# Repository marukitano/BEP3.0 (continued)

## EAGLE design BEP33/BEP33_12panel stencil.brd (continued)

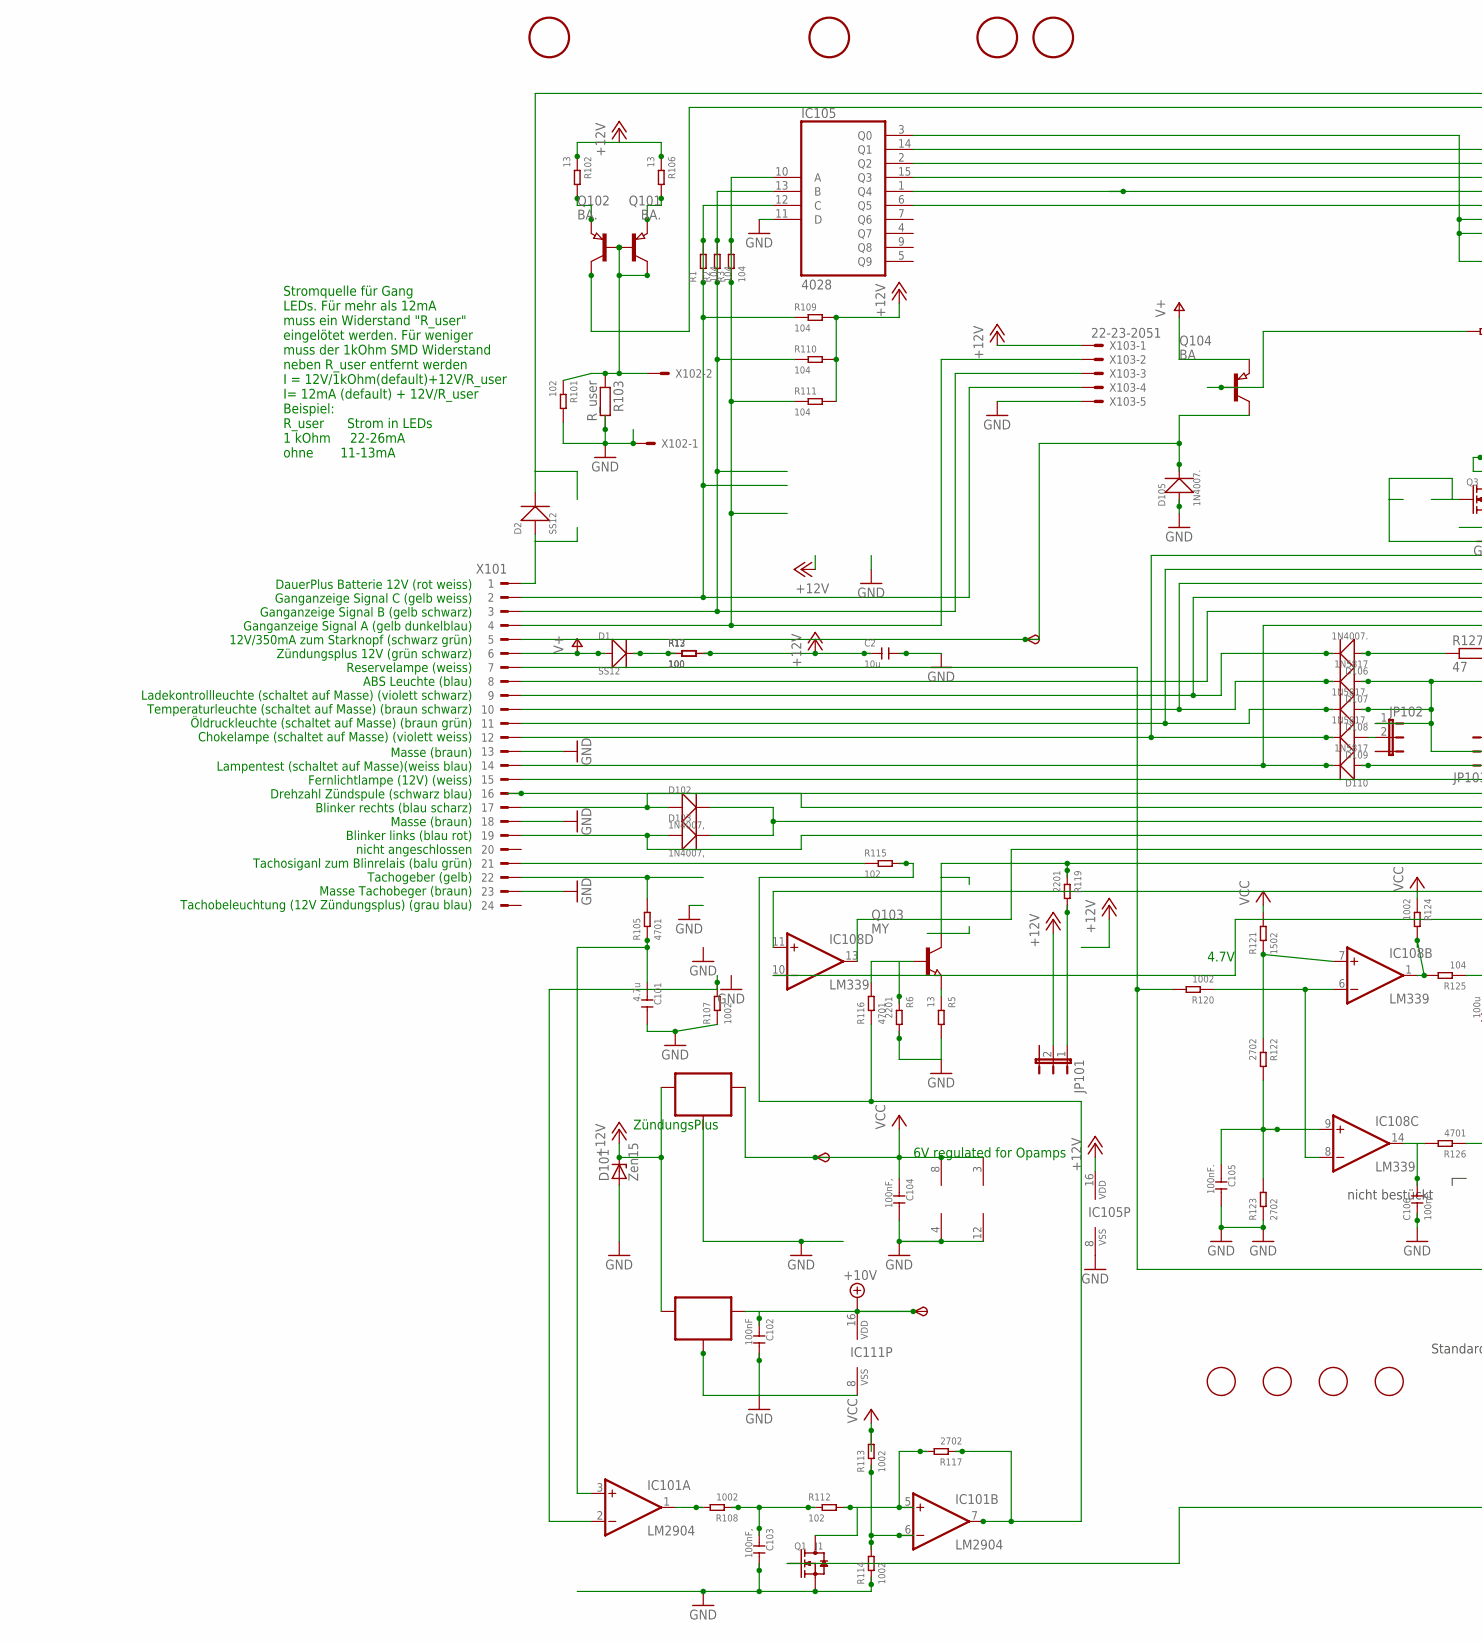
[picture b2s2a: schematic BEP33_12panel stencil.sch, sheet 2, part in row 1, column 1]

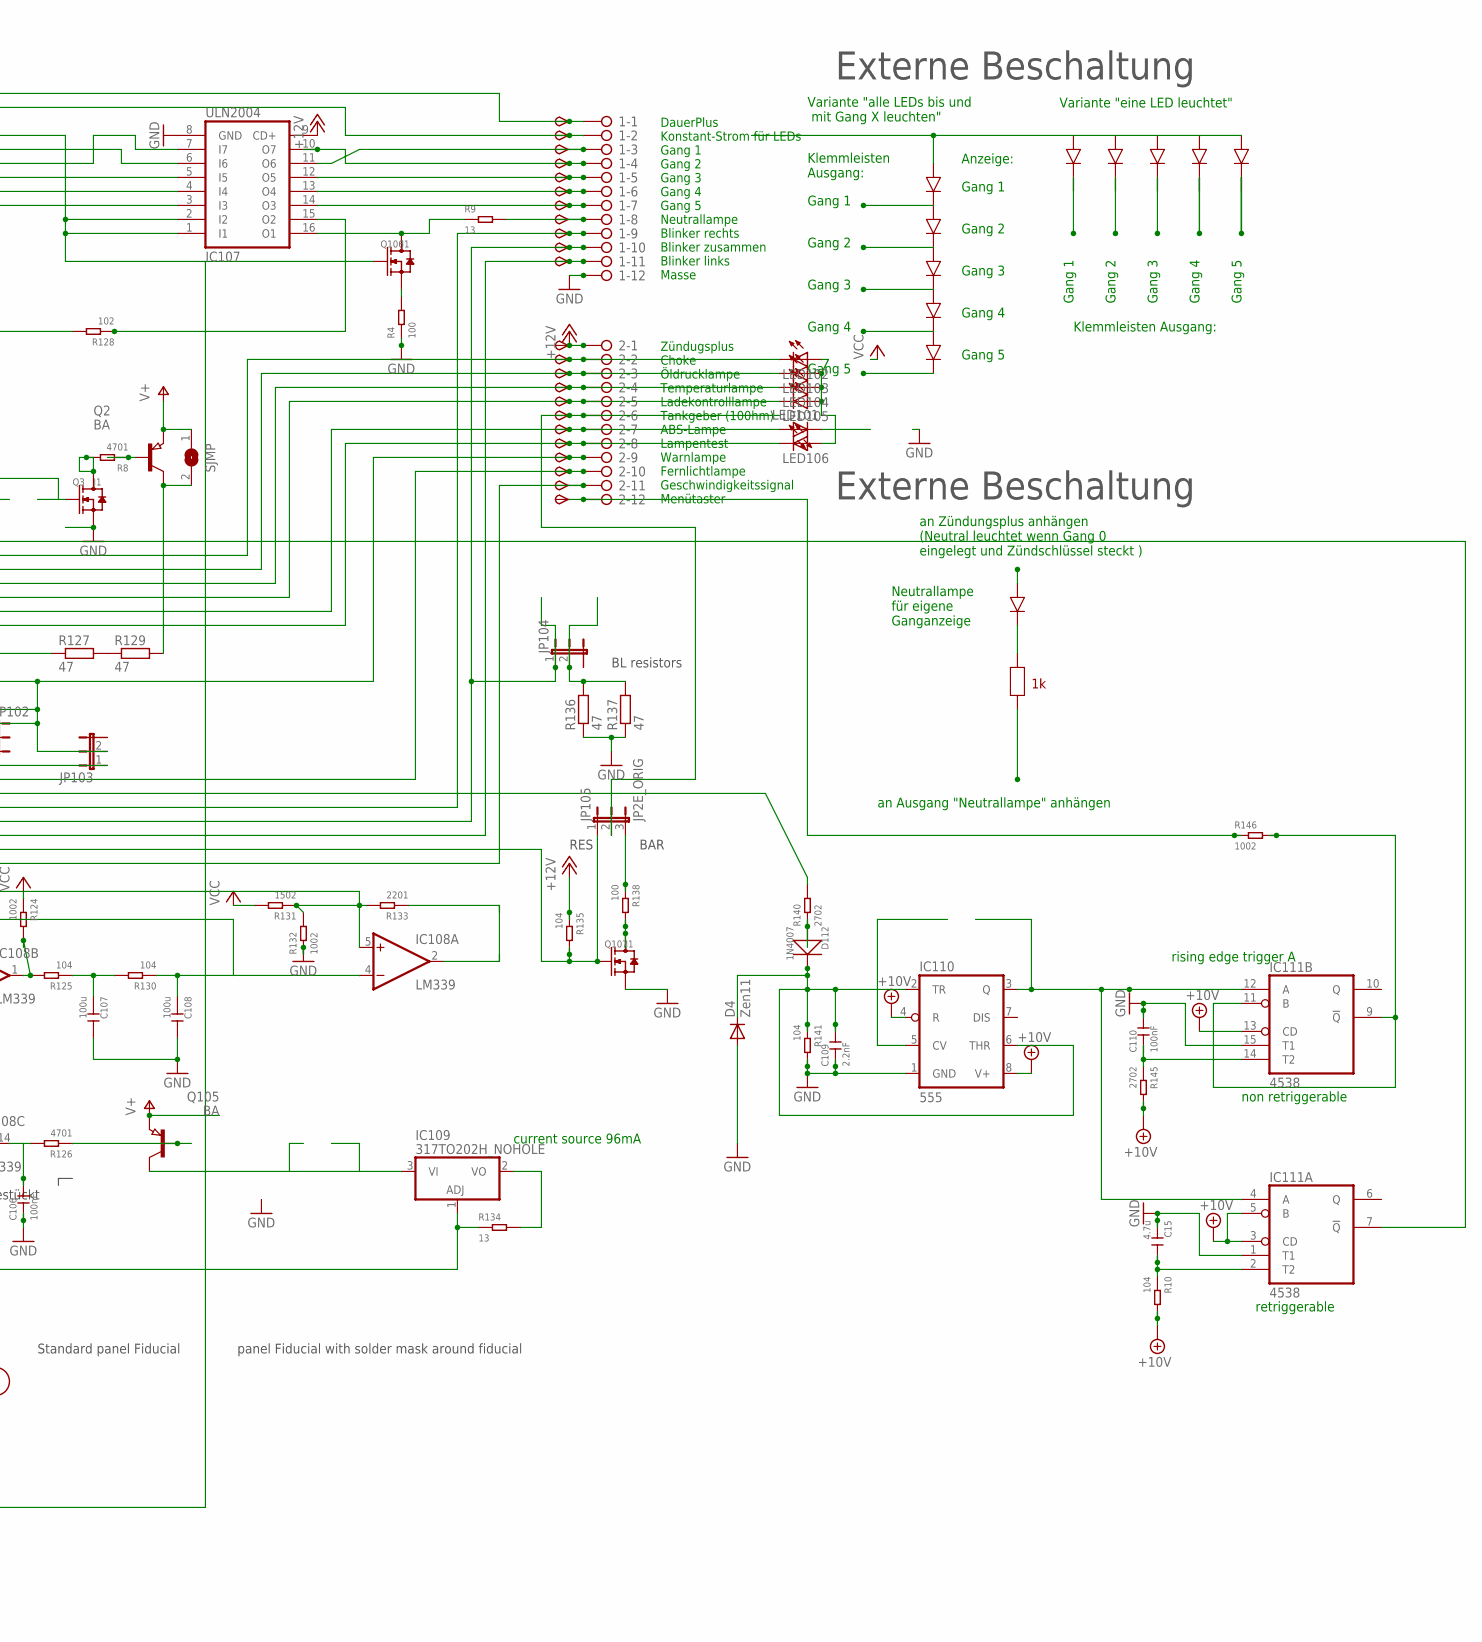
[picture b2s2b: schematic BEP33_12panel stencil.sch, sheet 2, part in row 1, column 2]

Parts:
1, 2: 2081-1132; 12-PIN
6V, 10V: TPSB2.0; B2.0
C2: 10u; C1206
C15, C101: 4.7u; C0805
C102, C110: 100nF; C0805
C103, C104: 100nF,; C0805
C105, C106: 100nF.; C0805
C107, C108: 100u; C1206
C109: 2.2nF; C0805
D1, D2: SS12; DO-214AC_SLIM
D4: Zen11; SOD-123_MINI-SMA
D101: Zen15; DO214AA
D102, D103: 1N4007,; DO-214AC
D105, D106: 1N4007.; DO-214AC
D107, D110: 1N5817; DO-214AC_SLIM
D108, D109: 1N5817.; DO-214AC_SLIM
D112: 1N4007; DO-214AC
FID101, FID102, FID103, FID104: FIDUCIAL; FIDUCIAL_1MM
IC101: LM2904; SO08
IC102: 78L06; SOT89_ROUND
IC104: 78L10; SOT89_ROUND
IC105: 4028; SO16
IC107: ULN2004; SO16
IC108: LM339; SO14
IC109: 317TO202H_NOHOLE; TO220H_NOHOLE
IC110: 555; SO08
IC111: 4538; SO16
JP101, JP102, JP103, JP104: JP2EJP2_SMALLPADS; JP2_SMALLPADS
JP105: JP2E_ORIG; JP2_ORIG_SMALLPADS
LED101, LED102, LED103, LED104, LED105, LED106: LEDLD260; LD260
Q1, Q3, Q106, Q107: J1; SOT-23
Q2, Q104, Q105: BA; SOT89
Q101, Q102: BA.; SOT89
Q103: MY; SOT89
R1, R2, R3, R10, R109, R110, R111, R125, R130, R135, R141: 104; R0805
R4, R12, R13, R138: 100; R0805
R5, R9, R102, R106, R134: 13; R1206
R6, R119, R133: 2201; R0805
R8, R105, R116, R126: 4701; R0805
R101, R112, R115, R128: 102; R0805
R103: R_user; R0805
R107, R108, R113, R114, R120, R124, R132, R146: 1002; R0805
R117, R122, R123, R140, R145: 2702; R0805
R121, R131: 1502; R0805
R127, R129, R136, R137: 47; V235/17_1MM
SJMP: SJ
START: TPSB2.0; B2.0
TP1, TP2, TP3, TP4, TP5, TP6, TP7, TP8, TP9, TP10, TP11, TP12, TP13, TP16, TP17, TP18, TP19, TP21, TP22, TP23, TP25, TP26: TPSB2.0; B2.0
TP24: TPSB1,27; B1,27
U$13, U$18, U$21, U$22: STC; STENCIL_HOLE
X101: CON_BMWV2; 24-PIN_V2
X102: 22-23-2021
X103: 22-23-2051

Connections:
+10V: 10V.TP, C102.1, IC104.1 (OUT), IC110.4 (R), IC110.8 (V+), IC111.3 (CD), IC111.5 (B), IC111.13 (CD), IC111.16 (VDD), R10.2, R145.2; also elsewhere on the board
+12V: 2.1, C2.1, D101.C, IC102.3 (IN), IC104.3 (IN), IC105.16 (VDD), IC107.9 (CD+), JP101.2, R12.2, R13.2, R102.1, R106.1, R109.2, R110.2, R111.2, R135.1, TP12.TP, X103.1; also elsewhere on the board
+12V1: 2.11, Q103.2 (C), R119.1, TP26.TP
GND: 1.12, C2.2, C15.1, C101.2, C102.2, C103.2, C104.2, C105.2, C106.1, C107.2, C108.2, C109.1, C110.2, D4.A, D101.A, D105.1 (+), IC101.4 (V-), IC102.2 (GND), IC102.2@1 (GND), IC104.2 (GND), IC104.2@1 (GND), IC105.8 (VSS), IC105.11 (D), IC107.8 (GND), IC108.12 (GND), IC110.1 (GND), IC111.1 (T1), IC111.8 (VSS), IC111.15 (T1), Q1.2 (S), Q3.2 (S), Q107.2 (S), R4.1, R5.2, R6.2, R101.2, R103.2, R107.1, R114.1, R123.1, R132.1, R136.1, R137.1, R141.2, X101.13, X101.18, X101.23, X102.1, X103.5; also elsewhere on the board
unnamed: 2.9, D107.1 (+), D108.1 (+), JP102.1, JP103.2, TP24.TP
unnamed: IC105.10 (A), R3.1, R3.2, R111.1, X101.4, X103.2
unnamed: IC105.13 (B), R2.1, R2.2, R110.1, X101.3, X103.3
unnamed: 2.7, LED101.A, TP22.TP, X101.8
unnamed: Q101.3 (E), R102.2
unnamed: Q2.1 (B), R8.1
unnamed: IC101.2 (-IN), R107.2
unnamed: R127.2, R129.1
unnamed: Q102.3 (E), R106.2
unnamed: D105.2 (-), Q104.2 (C), START.TP, X101.5
unnamed: 2.2, D109.2 (-), LED102.K (C), TP16.TP, X101.12
unnamed: 2.3, D108.2 (-), LED103.K (C), TP17.TP, X101.11
unnamed: 2.4, D107.2 (-), LED104.K (C), TP18.TP, X101.10
unnamed: IC109.3 (VI), Q105.2 (C)
unnamed: IC108.6 (-IN), IC108.8 (-IN), R120.1
unnamed: IC105.12 (C), R1.1, R1.2, R109.1, X101.2, X103.4
unnamed: IC105.15 (Q3), IC107.5 (I5)
unnamed: 2.8, D110.2 (-), LED106.K (C), TP23.TP, X101.14
unnamed: 1.9, D102.1 (+), TP9.TP, X101.17
unnamed: 1.11, D103.1 (+), TP11.TP, X101.19
unnamed: IC111.9 (!Q), IC111.11 (B), R146.2
unnamed: R105.2, X101.22
unnamed: C101.1, IC101.3 (+IN), R105.1
unnamed: 1.6, IC107.13 (O4), TP6.TP
unnamed: 1.7, IC107.14 (O3), TP7.TP
unnamed: D1.2 (-), R12.1, R13.1
unnamed: 2.6, JP105.2, TP21.TP
unnamed: JP101.1, R119.2
unnamed: C105.1, IC108.9 (+IN), R122.2, R123.2
unnamed: C106.2, IC108.14 (OUT), R126.2
unnamed: Q3.3 (D), R8.2
unnamed: IC109.1 (ADJ), R120.2, R134.1, X101.7
unnamed: Q105.1 (B), R126.1
unnamed: IC105.2 (Q2), IC107.7 (I7)
unnamed: 1.3, IC107.11 (O6), TP3.TP
unnamed: 1.5, IC107.12 (O5), TP5.TP
unnamed: LED102.A, LED103.A, LED104.A, LED105.A, LED106.A
unnamed: R140.2, X101.16
unnamed: Q104.1 (B), R128.2
unnamed: IC105.3 (Q0), IC107.1 (I1), IC107.2 (I2), Q1.1 (G), Q106.1 (G)
unnamed: C107.1, R125.1, R130.2
unnamed: C108.1, IC108.4 (-IN), IC108.10 (-IN), R130.1
unnamed: IC108.5 (+IN), IC108.11 (+IN), R131.1, R132.2, R133.2
unnamed: Q107.3 (D), R138.2
unnamed: IC111.7 (!Q), Q3.1 (G)
unnamed: IC105.1 (Q4), IC107.4 (I4)
unnamed: R115.1, X101.21
unnamed: IC107.16 (O1), Q106.3 (D), R9.1
unnamed: 2.10, TP25.TP, X101.15
unnamed: D106.1 (+), R127.1
unnamed: 2.5, D106.2 (-), LED105.K (C), TP19.TP, X101.9
unnamed: IC105.14 (Q1), IC107.6 (I6)
unnamed: Q101.1 (B), Q102.1 (B), Q102.2 (C), R101.1, R103.1, X102.2
unnamed: 1.8, R9.2, TP8.TP
unnamed: 1.2, Q101.2 (C), TP2.TP
unnamed: IC108.13 (OUT), JP105.1, Q107.1 (G), R135.2
unnamed: IC105.6 (Q5), IC107.3 (I3)
unnamed: IC109.2 (VO), R134.2
unnamed: 1.4, IC107.10 (O7), TP4.TP
unnamed: 1.1, D2.2 (-), TP1.TP
unnamed: IC108.7 (+IN), R121.1, R122.1
unnamed: Q106.2 (S), R4.2
unnamed: Q103.1 (B), R6.1, R116.2
unnamed: IC110.3 (Q), IC111.4 (A), IC111.12 (A)
unnamed: D112.1 (+), R140.1
unnamed: IC107.15 (O2), R128.1
unnamed: C110.1, IC111.14 (T2), R145.1
unnamed: 2.12, R146.1, TP13.TP
unnamed: D2.1 (+), X101.1
unnamed: IC101.1 (OUT), R108.2
unnamed: 1.10, D102.2 (-), D103.2 (-), JP104.1, TP10.TP
unnamed: JP104.2, R136.2, R137.2
unnamed: D109.1 (+), JP102.2
unnamed: C103.1, R108.1, R112.1
unnamed: IC101.5 (+IN), Q1.3 (D), R112.2, R117.2
unnamed: D110.1 (+), JP103.1
unnamed: JP105.3, R138.1
unnamed: Q103.3 (E), R5.1
unnamed: IC101.6 (-IN), R113.1, R114.2
unnamed: C109.2, D4.C, D112.2 (-), IC110.2 (TR), IC110.6 (THR), R141.1
unnamed: C15.2, IC111.2 (T2), R10.1
unnamed: Q2.2 (C), R129.2, SJMP.2
unnamed: IC101.7 (OUT), R115.2, R116.1, R117.1
unnamed: IC108.2 (OUT), R133.1
unnamed: IC108.1 (OUT), R124.2, R125.2
V+: D1.1 (+), Q2.3 (E), Q104.3 (E), Q105.3 (E), SJMP.1, X101.6; also elsewhere on the board
VCC: 6V.TP, C104.1, IC101.8 (V+), IC102.1 (OUT), IC108.3 (V+), R113.2, R121.2, R124.1, R131.2; also elsewhere on the board

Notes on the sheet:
6V regulated for Opamps
current source 96mA
ZündungsPlus
Zündugsplus Choke Öldrucklampe Temperaturlampe Ladekontrolllampe Tankgeber (100hm) ABS-Lampe Lampentest Warnlampe Fernlichtlampe Geschwindigkeitssignal Menütaster
DauerPlus Konstant-Strom für LEDs Gang 1 Gang 2 Gang 3 Gang 4 Gang 5 Neutrallampe Blinker rechts Blinker zusammen Blinker links Masse
DauerPlus Batterie 12V (rot weiss) Ganganzeige Signal C (gelb weiss) Ganganzeige Signal B (gelb schwarz) Ganganzeige Signal A (gelb dunkelblau) 12V/350mA zum Starknopf (schwarz grün) Zündungsplus 12V (grün schwarz) Reservelampe (weiss) ABS Leuchte (blau) Ladekontrollleuchte (schaltet auf Masse) (vi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
Masse (braun) Lampentest (schaltet auf Masse)(weiss blau) Fernlichtlampe (12V) (weiss) Drehzahl Zündspule (schwarz blau) Blinker rechts (blau scharz) Masse (braun) Blinker links (blau rot) nicht angeschlossen Tachosiganl zum Blinrelais (balu grün) Tachogeber (gelb) Masse Tachobeger (braun) Tachobel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
4.7V
Stromquelle für Gang LEDs. Für mehr als 12mA muss ein Widerstand "R_user" eingelötet werden. Für weniger muss der 1kOhm SMD Widerstand neben R_user entfernt werden I = 12V/1kOhm(default)+12V/R_user I= 12mA (default) + 12V/R_user Beispiel: R_user Strom in LEDs 1 kOhm 22-26mA ohne 11-13mA
Gang 1
Gang 2
Gang 3
Gang 4
Gang 5
Variante "eine LED leuchtet"
Variante "alle LEDs bis und mit Gang X leuchten"
Klemmleisten Ausgang:
Klemmleisten Ausgang:
an Zündungsplus anhängen (Neutral leuchtet wenn Gang 0 eingelegt und Zündschlüssel steckt )
an Ausgang "Neutrallampe" anhängen
Neutrallampe für eigene Ganganzeige
Externe Beschaltung
Anzeige:
nicht bestückt
rising edge trigger A
BAR
RES
BL resistors
Standard panel Fiducial
panel Fiducial with solder mask around fiducial
non retriggerable
retriggerable

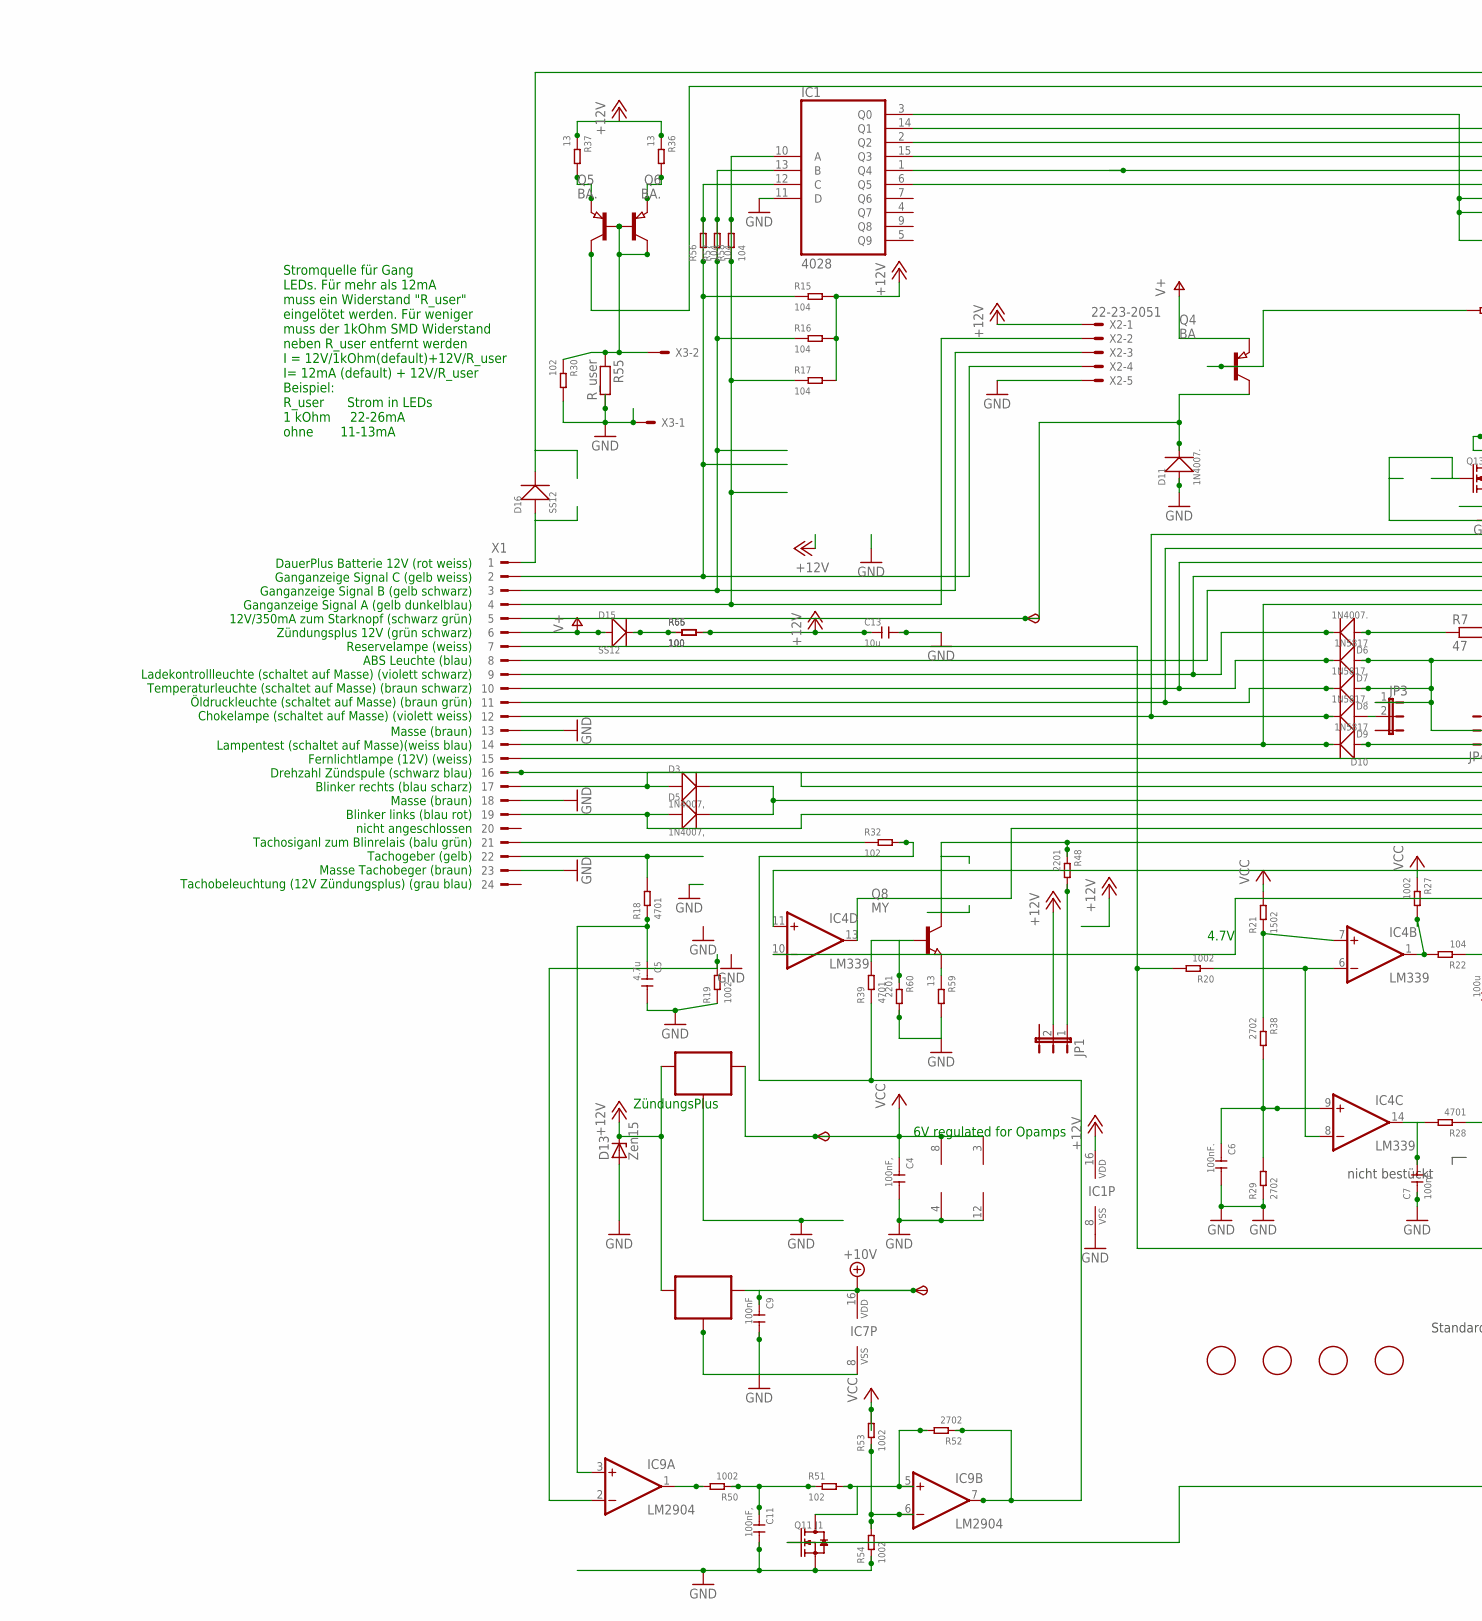
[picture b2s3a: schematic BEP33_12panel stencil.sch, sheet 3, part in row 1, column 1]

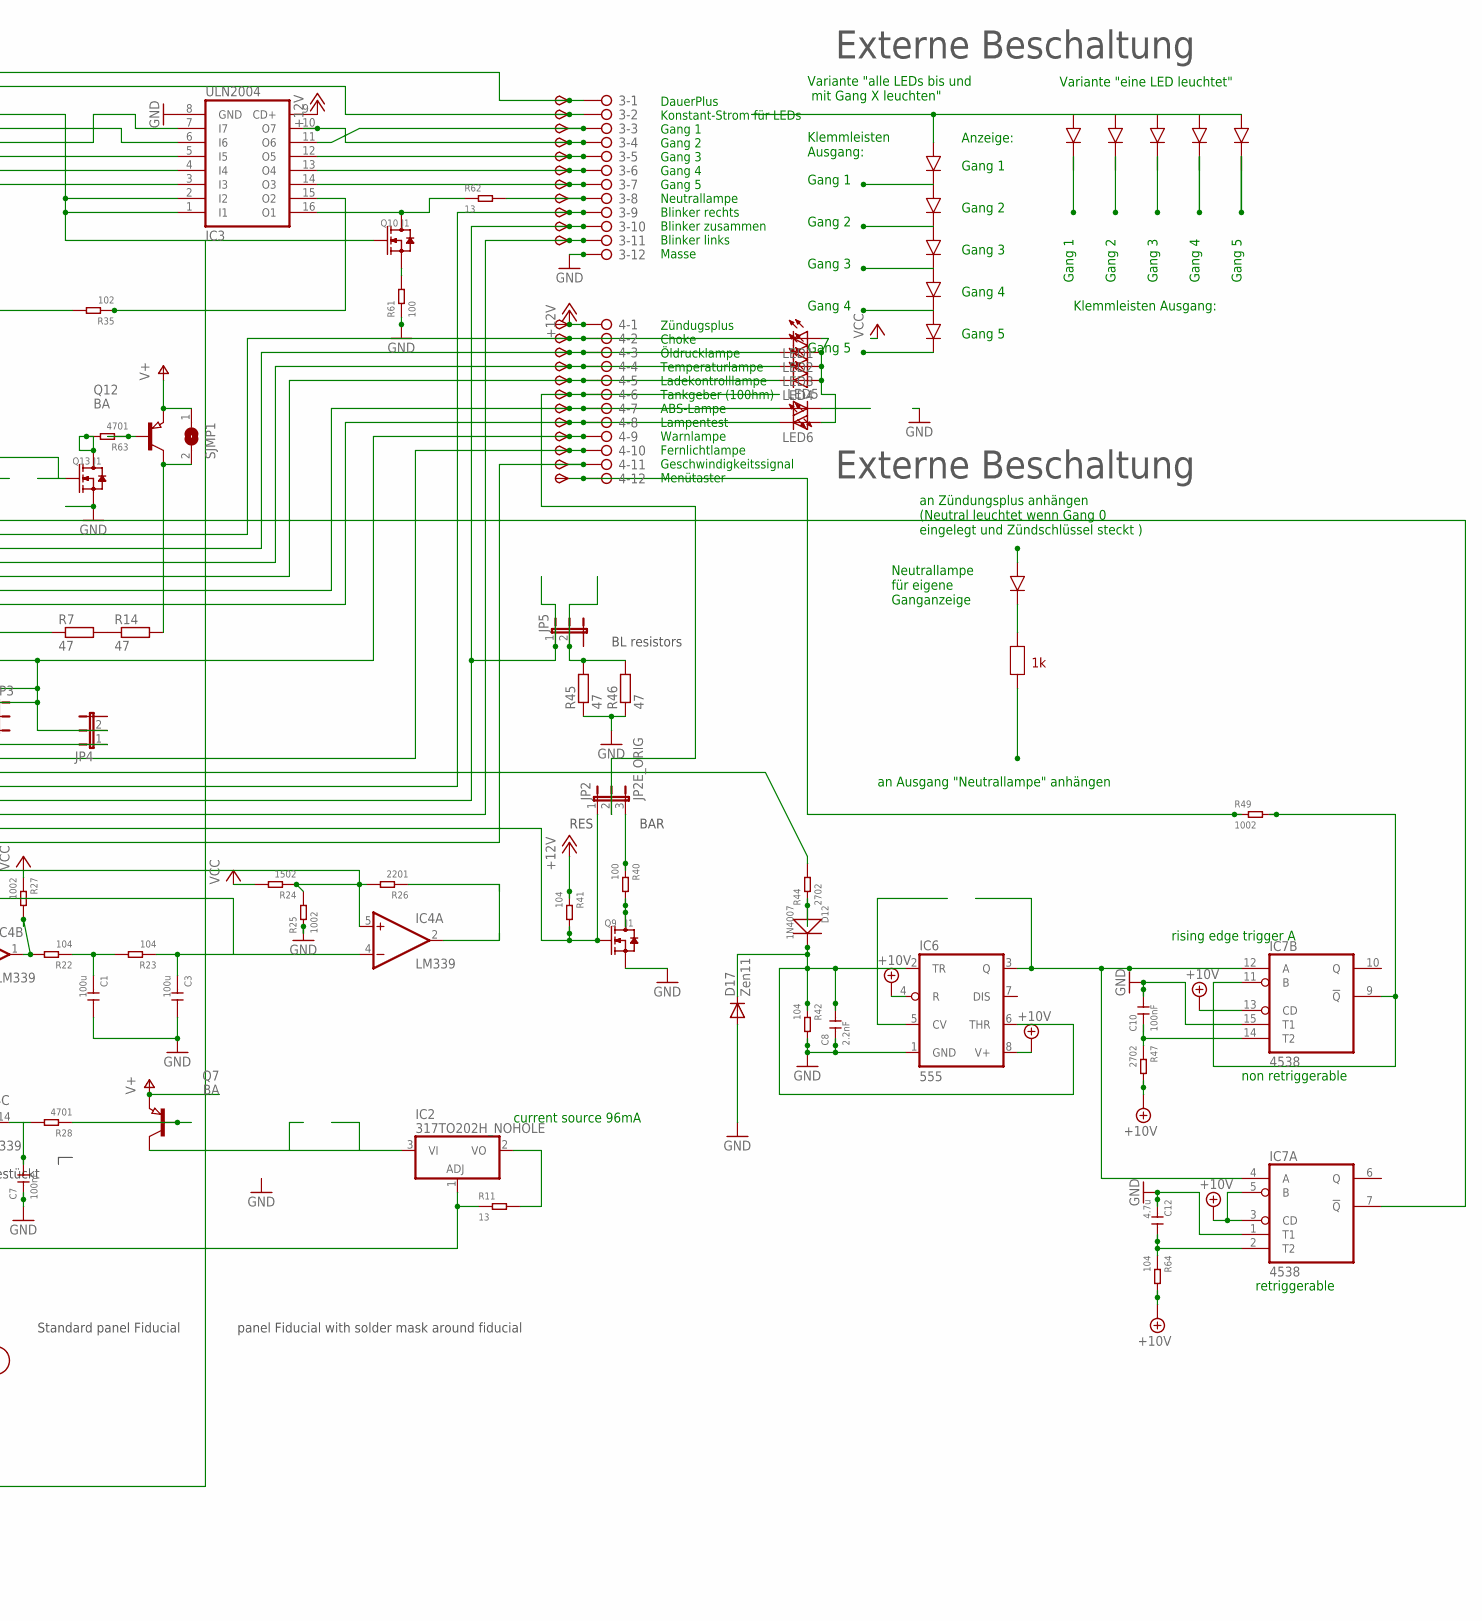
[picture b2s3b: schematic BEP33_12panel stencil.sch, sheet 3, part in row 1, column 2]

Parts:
3, 4: 2081-1132; 12-PIN
6V1, 10V1: TPSB2.0; B2.0
C1, C3: 100u; C1206
C4, C11: 100nF,; C0805
C5, C12: 4.7u; C0805
C6, C7: 100nF.; C0805
C8: 2.2nF; C0805
C9, C10: 100nF; C0805
C13: 10u; C1206
D3, D5: 1N4007,; DO-214AC
D6, D11: 1N4007.; DO-214AC
D7, D10: 1N5817; DO-214AC_SLIM
D8, D9: 1N5817.; DO-214AC_SLIM
D12: 1N4007; DO-214AC
D13: Zen15; DO214AA
D15, D16: SS12; DO-214AC_SLIM
D17: Zen11; SOD-123_MINI-SMA
FID3, FID4, FID5, FID6: FIDUCIAL; FIDUCIAL_1MM
IC1: 4028; SO16
IC2: 317TO202H_NOHOLE; TO220H_NOHOLE
IC3: ULN2004; SO16
IC4: LM339; SO14
IC5: 78L06; SOT89_ROUND
IC6: 555; SO08
IC7: 4538; SO16
IC8: 78L10; SOT89_ROUND
IC9: LM2904; SO08
JP1, JP3, JP4, JP5: JP2EJP2_SMALLPADS; JP2_SMALLPADS
JP2: JP2E_ORIG; JP2_ORIG_SMALLPADS
LED1, LED2, LED3, LED4, LED5, LED6: LEDLD260; LD260
Q4, Q7, Q12: BA; SOT89
Q5, Q6: BA.; SOT89
Q8: MY; SOT89
Q9, Q10, Q11, Q13: J1; SOT-23
R7, R14, R45, R46: 47; V235/17_1MM
R11, R36, R37, R59, R62: 13; R1206
R15, R16, R17, R22, R23, R41, R42, R56, R57, R58, R64: 104; R0805
R18, R28, R39, R63: 4701; R0805
R19, R20, R25, R27, R49, R50, R53, R54: 1002; R0805
R21, R24: 1502; R0805
R26, R48, R60: 2201; R0805
R29, R38, R44, R47, R52: 2702; R0805
R30, R32, R35, R51: 102; R0805
R40, R61, R65, R66: 100; R0805
R55: R_user; R0805
SJMP1: SJ
START1: TPSB2.0; B2.0
TP14, TP15, TP20, TP27, TP28, TP29, TP30, TP31, TP32, TP33, TP34, TP35, TP36, TP37, TP38, TP39, TP40, TP41, TP43, TP44, TP45, TP46: TPSB2.0; B2.0
TP42: TPSB1,27; B1,27
X1: CON_BMWV2; 24-PIN_V2
X2: 22-23-2051
X3: 22-23-2021

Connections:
+10V: 10V1.TP, C9.1, IC6.4 (R), IC6.8 (V+), IC7.3 (CD), IC7.5 (B), IC7.13 (CD), IC7.16 (VDD), IC8.1 (OUT), R47.2, R64.2; also elsewhere on the board
+12V: 4.1, C13.1, D13.C, IC1.16 (VDD), IC3.9 (CD+), IC5.3 (IN), IC8.3 (IN), JP1.2, R15.2, R16.2, R17.2, R36.1, R37.1, R41.1, R65.2, R66.2, TP45.TP, X2.1; also elsewhere on the board
+12V2: 4.11, Q8.2 (C), R48.1, TP44.TP
GND: 3.12, C1.2, C3.2, C4.2, C5.2, C6.2, C7.1, C8.1, C9.2, C10.2, C11.2, C12.1, C13.2, D11.1 (+), D13.A, D17.A, IC1.8 (VSS), IC1.11 (D), IC3.8 (GND), IC4.12 (GND), IC5.2 (GND), IC5.2@1 (GND), IC6.1 (GND), IC7.1 (T1), IC7.8 (VSS), IC7.15 (T1), IC8.2 (GND), IC8.2@1 (GND), IC9.4 (V-), Q9.2 (S), Q11.2 (S), Q13.2 (S), R19.1, R25.1, R29.1, R30.2, R42.2, R45.1, R46.1, R54.1, R55.2, R59.2, R60.2, R61.1, X1.13, X1.18, X1.23, X2.5, X3.1; also elsewhere on the board
unnamed: R7.2, R14.1
unnamed: 4.9, D7.1 (+), D8.1 (+), JP3.1, JP4.2, TP42.TP
unnamed: IC1.10 (A), R17.1, R58.1, R58.2, X1.4, X2.2
unnamed: IC1.13 (B), R16.1, R57.1, R57.2, X1.3, X2.3
unnamed: D11.2 (-), Q4.2 (C), START1.TP, X1.5
unnamed: IC1.12 (C), R15.1, R56.1, R56.2, X1.2, X2.4
unnamed: 4.7, LED5.A, TP40.TP, X1.8
unnamed: 4.2, D9.2 (-), LED1.K (C), TP35.TP, X1.12
unnamed: 4.3, D8.2 (-), LED2.K (C), TP36.TP, X1.11
unnamed: 4.4, D7.2 (-), LED3.K (C), TP37.TP, X1.10
unnamed: 4.8, D10.2 (-), LED6.K (C), TP41.TP, X1.14
unnamed: 3.9, D3.1 (+), TP32.TP, X1.17
unnamed: 3.11, D5.1 (+), TP34.TP, X1.19
unnamed: R18.2, X1.22
unnamed: C5.1, IC9.3 (+IN), R18.1
unnamed: IC4.1 (OUT), R22.2, R27.2
unnamed: C1.1, R22.1, R23.2
unnamed: C3.1, IC4.4 (-IN), IC4.10 (-IN), R23.1
unnamed: IC4.5 (+IN), IC4.11 (+IN), R24.1, R25.2, R26.2
unnamed: C6.1, IC4.9 (+IN), R29.2, R38.2
unnamed: C7.2, IC4.14 (OUT), R28.2
unnamed: Q7.1 (B), R28.1
unnamed: IC1.2 (Q2), IC3.7 (I7)
unnamed: 3.5, IC3.12 (O5), TP28.TP
unnamed: IC1.1 (Q4), IC3.4 (I4)
unnamed: 4.10, TP43.TP, X1.15
unnamed: 4.5, D6.2 (-), LED4.K (C), TP38.TP, X1.9
unnamed: D6.1 (+), R7.1
unnamed: IC1.6 (Q5), IC3.3 (I3)
unnamed: 3.4, IC3.10 (O7), TP27.TP
unnamed: IC2.1 (ADJ), R11.1, R20.2, X1.7
unnamed: IC4.6 (-IN), IC4.8 (-IN), R20.1
unnamed: 3.2, Q6.2 (C), TP15.TP
unnamed: 3.1, D16.2 (-), TP14.TP
unnamed: R44.2, X1.16
unnamed: IC1.15 (Q3), IC3.5 (I5)
unnamed: 3.6, IC3.13 (O4), TP29.TP
unnamed: 3.7, IC3.14 (O3), TP30.TP
unnamed: 4.6, JP2.2, TP39.TP
unnamed: LED1.A, LED2.A, LED3.A, LED4.A, LED6.A
unnamed: Q4.1 (B), R35.2
unnamed: IC1.3 (Q0), IC3.1 (I1), IC3.2 (I2), Q10.1 (G), Q11.1 (G)
unnamed: IC1.14 (Q1), IC3.6 (I6)
unnamed: 3.3, IC3.11 (O6), TP20.TP
unnamed: Q5.1 (B), Q5.2 (C), Q6.1 (B), R30.1, R55.1, X3.2
unnamed: Q6.3 (E), R37.2
unnamed: Q5.3 (E), R36.2
unnamed: IC4.7 (+IN), R21.1, R38.1
unnamed: IC9.2 (-IN), R19.2
unnamed: Q8.1 (B), R39.2, R60.1
unnamed: Q9.3 (D), R40.2
unnamed: IC2.2 (VO), R11.2
unnamed: IC2.3 (VI), Q7.2 (C)
unnamed: IC6.3 (Q), IC7.4 (A), IC7.12 (A)
unnamed: D12.1 (+), R44.1
unnamed: 3.10, D3.2 (-), D5.2 (-), JP5.1, TP33.TP
unnamed: JP5.2, R45.2, R46.2
unnamed: IC7.9 (!Q), IC7.11 (B), R49.2
unnamed: C10.1, IC7.14 (T2), R47.1
unnamed: JP1.1, R48.2
unnamed: IC3.15 (O2), R35.1
unnamed: 4.12, R49.1, TP46.TP
unnamed: D9.1 (+), JP3.2
unnamed: IC9.1 (OUT), R50.2
unnamed: C11.1, R50.1, R51.1
unnamed: IC9.5 (+IN), Q11.3 (D), R51.2, R52.2
unnamed: IC9.6 (-IN), R53.1, R54.2
unnamed: D10.1 (+), JP4.1
unnamed: JP2.3, R40.1
unnamed: IC4.13 (OUT), JP2.1, Q9.1 (G), R41.2
unnamed: R32.1, X1.21
unnamed: IC3.16 (O1), Q10.3 (D), R62.1
unnamed: D15.2 (-), R65.1, R66.1
unnamed: 3.8, R62.2, TP31.TP
unnamed: Q10.2 (S), R61.2
unnamed: D16.1 (+), X1.1
unnamed: Q8.3 (E), R59.1
unnamed: C8.2, D12.2 (-), D17.C, IC6.2 (TR), IC6.6 (THR), R42.1
unnamed: Q12.1 (B), R63.1
unnamed: Q13.3 (D), R63.2
unnamed: Q12.2 (C), R14.2, SJMP1.2
unnamed: IC9.7 (OUT), R32.2, R39.1, R52.1
unnamed: IC4.2 (OUT), R26.1
unnamed: IC7.7 (!Q), Q13.1 (G)
unnamed: C12.2, IC7.2 (T2), R64.1
V+: D15.1 (+), Q4.3 (E), Q7.3 (E), Q12.3 (E), SJMP1.1, X1.6; also elsewhere on the board
VCC: 6V1.TP, C4.1, IC4.3 (V+), IC5.1 (OUT), IC9.8 (V+), R21.2, R24.2, R27.1, R53.2; also elsewhere on the board

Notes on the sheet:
6V regulated for Opamps
current source 96mA
ZündungsPlus
Zündugsplus Choke Öldrucklampe Temperaturlampe Ladekontrolllampe Tankgeber (100hm) ABS-Lampe Lampentest Warnlampe Fernlichtlampe Geschwindigkeitssignal Menütaster
DauerPlus Konstant-Strom für LEDs Gang 1 Gang 2 Gang 3 Gang 4 Gang 5 Neutrallampe Blinker rechts Blinker zusammen Blinker links Masse
DauerPlus Batterie 12V (rot weiss) Ganganzeige Signal C (gelb weiss) Ganganzeige Signal B (gelb schwarz) Ganganzeige Signal A (gelb dunkelblau) 12V/350mA zum Starknopf (schwarz grün) Zündungsplus 12V (grün schwarz) Reservelampe (weiss) ABS Leuchte (blau) Ladekontrollleuchte (schaltet auf Masse) (vi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
Masse (braun) Lampentest (schaltet auf Masse)(weiss blau) Fernlichtlampe (12V) (weiss) Drehzahl Zündspule (schwarz blau) Blinker rechts (blau scharz) Masse (braun) Blinker links (blau rot) nicht angeschlossen Tachosiganl zum Blinrelais (balu grün) Tachogeber (gelb) Masse Tachobeger (braun) Tachobel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
4.7V
Stromquelle für Gang LEDs. Für mehr als 12mA muss ein Widerstand "R_user" eingelötet werden. Für weniger muss der 1kOhm SMD Widerstand neben R_user entfernt werden I = 12V/1kOhm(default)+12V/R_user I= 12mA (default) + 12V/R_user Beispiel: R_user Strom in LEDs 1 kOhm 22-26mA ohne 11-13mA
Gang 1
Gang 2
Gang 3
Gang 4
Gang 5
Variante "eine LED leuchtet"
Variante "alle LEDs bis und mit Gang X leuchten"
Klemmleisten Ausgang:
Klemmleisten Ausgang:
an Zündungsplus anhängen (Neutral leuchtet wenn Gang 0 eingelegt und Zündschlüssel steckt )
an Ausgang "Neutrallampe" anhängen
Neutrallampe für eigene Ganganzeige
Externe Beschaltung
Anzeige:
nicht bestückt
rising edge trigger A
BAR
RES
BL resistors
Standard panel Fiducial
panel Fiducial with solder mask around fiducial
non retriggerable
retriggerable
